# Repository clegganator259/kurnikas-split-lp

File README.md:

# kurnikas-split-lp
My attempt at designing my perfect split ergo keyboard

# Attribution

For the battery connector and led footprints @celolides fantastic [footprint library](https://github.com/ceoloide/ergogen-footprints)
For the choc v1 reversible footprints @ergogen + @infused-kim, @ceoloide, @grazfather, @nxtk improvements

For the videos that helped make this possible [Christian Sellig's wonderful video](https://www.youtube.com/watch?v=7UXsD7nSfDY)
# BOM
## PCB Components
|Component                            |                    Quantity|
|-------------------------------------|---------------------------:|
|kurnikas-split-lp PCB                |                           2|
|Nice nano v2 compatible board        |                           2|
|Choc v1 Key switches                 |                          64|
|SK6812 mini-e RGB                    |                          64|
|EC12/EC11 low profile encoder        |                           2|
|1N4148W SOD123 Diodes                | 64/66 if using EC11 Encoder|
|JST PH2 board connector              |                           2|
|3.7v Lipo battery thickness < 8mm    |                           2|
|JST PH2 male connectors for batteries|                           2|
|7 pin on/off toggle slide switch     |                           2|
|SKQGABE010 touch switch smd          |                           2|

## Case components
### Full case
|Component         | Quantity|
|------------------|--------:|
|8mm m2 standoffs  |       10|
|m2 flat top screws|       10|
|[Left hand faceplate](production/full-case-3dprint/face-plate-left.stl)| 1|
|[Right hand faceplate](production/full-case-3dprint/face-plate-right.stl)| 1|
|[Left hand Backplate](production/full-case-3dprint/base-plate-right.stl)| 1|
|[Right hand Backplate](production/full-case-3dprint/base-plate-left.stl)| 1|

### Sandwich Case
|Component                             | Quantity|
|--------------------------------------|--------:|
|m2x4mm chicago screws with max 3mm OD |       10|
|Faceplate ([laser cut](production/sandwich-case-laser-cut/faceplate.dxf)/[3d printed](production/sandwich-case-3dprint/faceplate.stl)) |2|
|Baseplate ([laser cut](production/sandwich-case-laser-cut/baseplate.dxf)/[3d printed](production/sandwich-case-3dprint/baseplate.stl)) |2|

## Making your own

For a more detailed tutorial please go to [the build tutorial](docs/tutorial.md)

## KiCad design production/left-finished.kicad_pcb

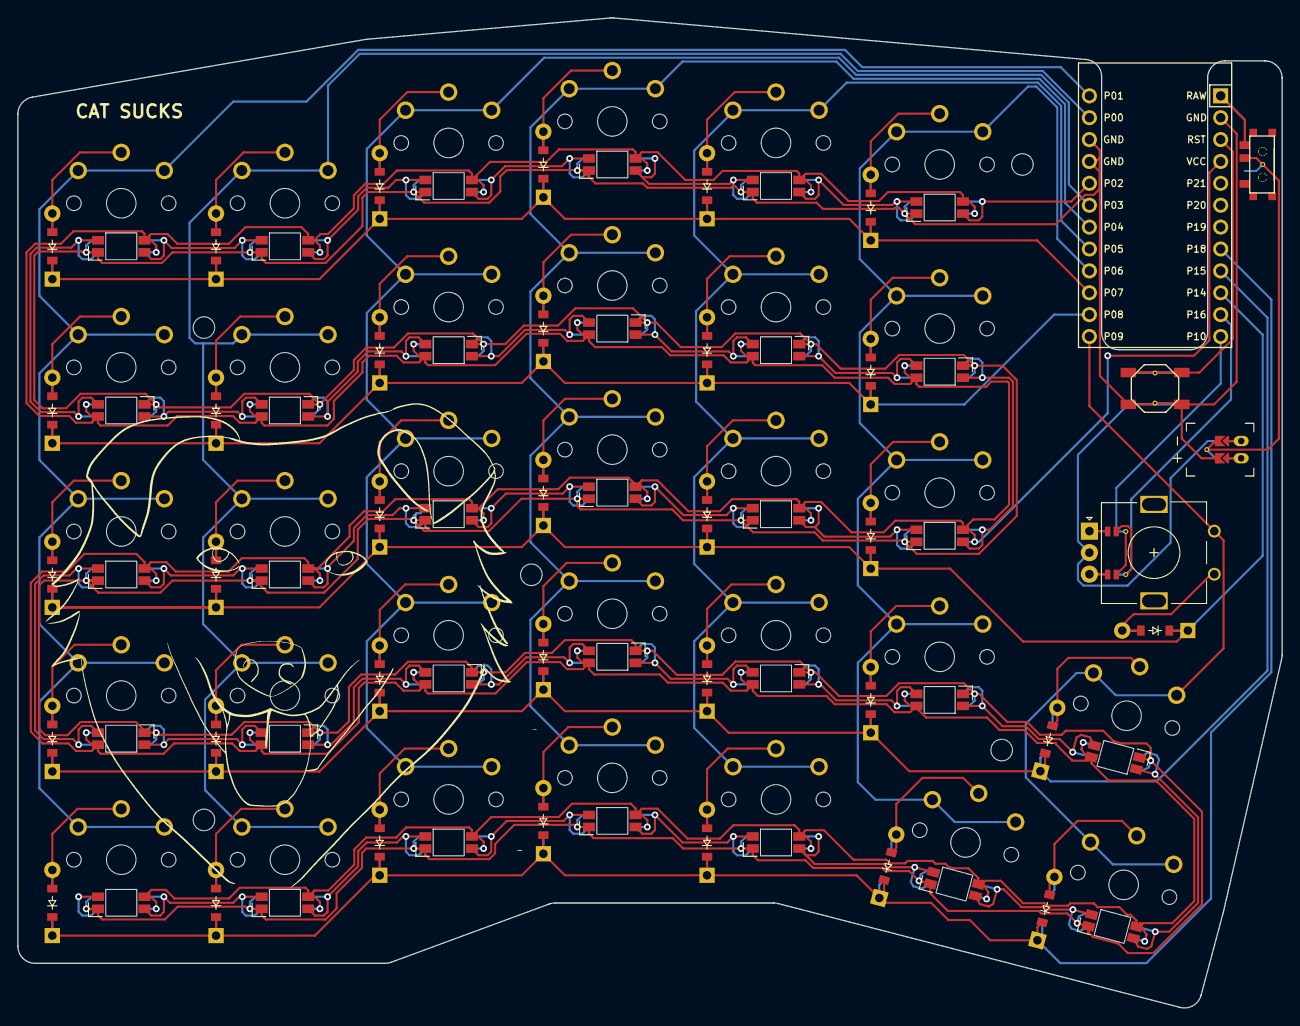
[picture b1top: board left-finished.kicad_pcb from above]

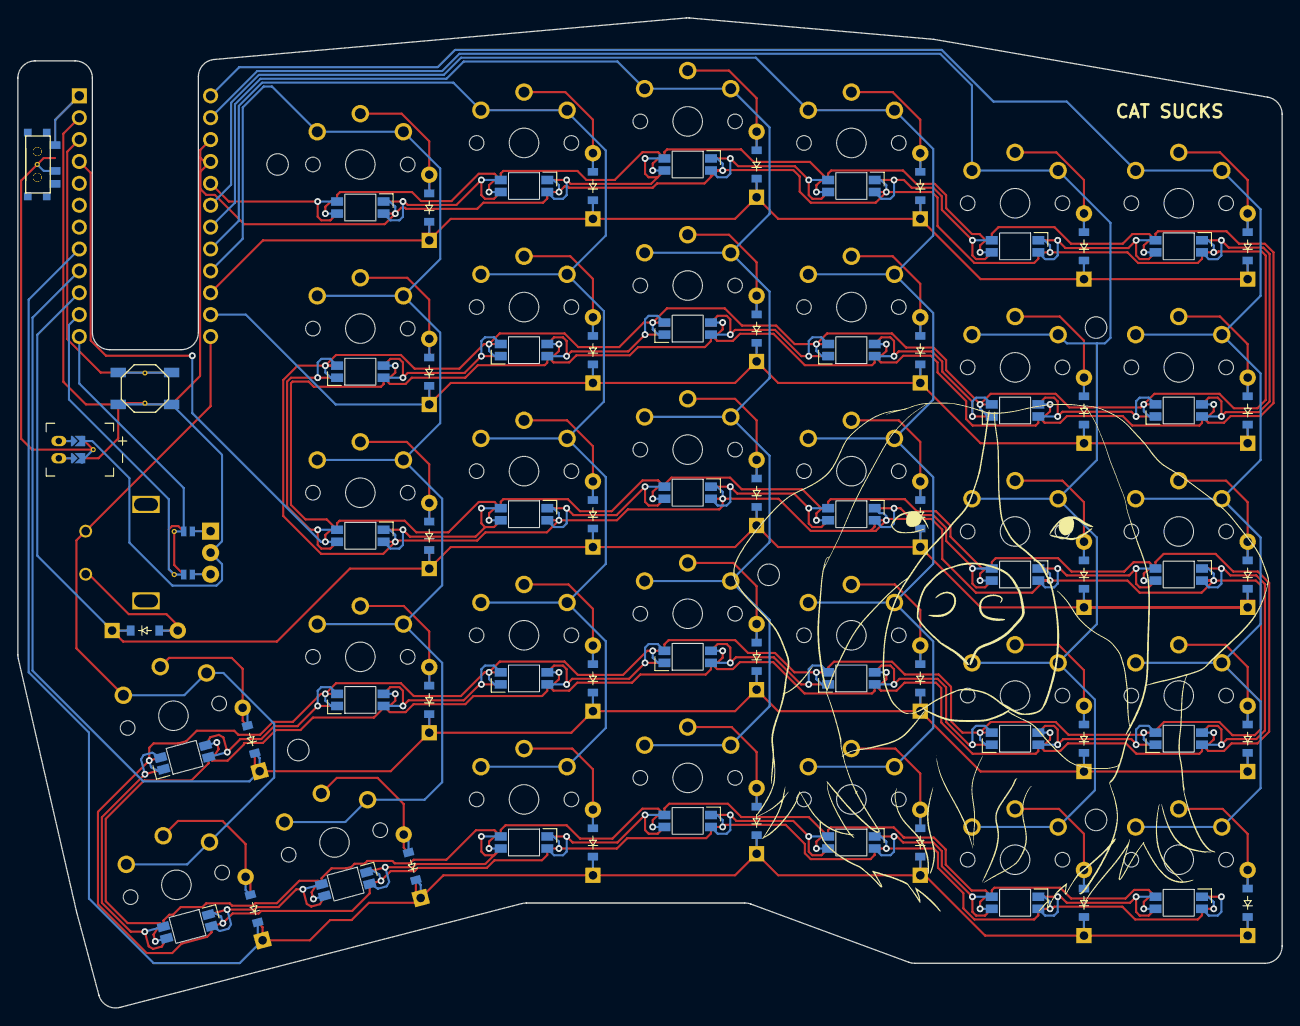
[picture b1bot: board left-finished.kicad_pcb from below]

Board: 2 copper layers, 146.8 x 114.9 mm, 108 parts (32 on the bottom side), 88 nets.

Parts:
B1, B2: SW_TACT_ALPS_SKQGABE010
D1, D2, D3, D4, D5, D6, D7, D8, D9, D10, D11, D12, D13, D14, D15, D16, D17, D18, D19, D20, D21, D22, D23, D24, D25, D26, D27, D28, D29, D30, D31, D32, D33: ComboDiode
J1, J2, J3, J4: Jumper
JST1: battery_connector_jst_ph_2
LED1, LED2, LED3, LED4, LED5, LED6, LED7, LED8, LED9, LED10, LED11, LED12, LED13, LED14, LED15, LED16, LED17, LED18, LED19, LED20, LED21, LED22, LED23, LED24, LED25, LED26, LED27, LED28, LED29, LED30, LED31, LED32: led_SK6812mini-e (per-key, reversible)
MCU1: ProMicro
ROT1: rotary_encoder
S1, S2, S3, S4, S5, S6, S7, S8, S9, S10, S11, S12, S13, S14, S15, S16, S17, S18, S19, S20, S21, S22, S23, S24, S25, S26, S27, S28, S29, S30, S31, S32: PG1350
T1, T2: SPDT_C128955

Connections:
GND: B1.1, B2.1, JST1.2, LED1.3, LED2.3, LED3.3, LED4.3, LED5.3, LED6.3, LED7.3, LED8.3, LED9.3, LED10.3, LED11.3, LED12.3, LED13.3, LED14.3, LED15.3, LED16.3, LED17.3, LED18.3, LED19.3, LED20.3, LED21.3, LED22.3, LED23.3, LED24.3, LED25.3, LED26.3, LED27.3, LED28.3, LED29.3, LED30.3, LED31.3, LED32.3, MCU1.2, MCU1.15, MCU1.16, ROT1.C
JST1_1: JST1.11, JST1.21, JST1.31
JST1_2: JST1.12, JST1.22, JST1.32
P0: MCU1.14, S6.1, S7.1, S8.1, S9.1, S10.1
P1: MCU1.13, S1.1, S2.1, S3.1, S4.1, S5.1
P2: LED17.2, MCU1.17
P3: MCU1.18, S11.1, S12.1, S13.1, S14.1, S15.1
P4: MCU1.19, S16.1, S17.1, S18.1, S19.1, S20.1
P5: MCU1.20, S21.1, S22.1, S23.1, S24.1, S25.1
P6: MCU1.21, S26.1, S27.1, S28.1, S29.1, S30.1
P7: D5.1, D10.1, D15.1, D20.1, D25.1, D29.1, MCU1.22
P8: D4.1, D9.1, D14.1, D19.1, D24.1, D28.1, MCU1.23
P9: MCU1.24, ROT1.1, S31.1, S32.1
P10: J2.1, J3.1, MCU1.12
P14: D3.1, D8.1, D13.1, D18.1, D23.1, D27.1, D33.1, MCU1.10
P15: D2.1, D7.1, D12.1, D17.1, D22.1, D26.1, D32.1, MCU1.9
P16: J1.1, J4.1, MCU1.11
P18: D1.1, D6.1, D11.1, D16.1, D21.1, D30.1, D31.1, MCU1.8
RAW: MCU1.1, T1.3, T2.1
RB_ROW: D33.2, ROT1.2
RST: B1.2, B2.2, MCU1.3
VCC: LED1.1, LED2.1, LED3.1, LED4.1, LED5.1, LED6.1, LED7.1, LED8.1, LED9.1, LED10.1, LED11.1, LED12.1, LED13.1, LED14.1, LED15.1, LED16.1, LED17.1, LED18.1, LED19.1, LED20.1, LED21.1, LED22.1, LED23.1, LED24.1, LED25.1, LED26.1, LED27.1, LED28.1, LED29.1, LED30.1, LED31.1, LED32.1, MCU1.4
index_bottom: D22.2, S22.2
index_home: D23.2, S23.2
index_mod: D21.2, S21.2
index_num: D25.2, S25.2
index_top: D24.2, S24.2
inner_bottom: D26.2, S26.2
inner_bottom_thumbs: D31.2, S31.2
inner_home: D27.2, S27.2
inner_num: D29.2, S29.2
inner_top: D28.2, S28.2
inner_top_thumbs: D32.2, S32.2
led_1: LED15.2, LED17.4
led_2: LED12.2, LED15.4
led_3: LED9.2, LED12.4
led_4: LED6.2, LED9.4
led_5: LED3.2, LED6.4
led_6: LED3.4, LED21.2
led_7: LED21.4, LED23.2
led_8: LED23.4, LED25.2
led_9: LED25.4, LED27.2
led_10: LED27.4, LED29.2
led_11: LED29.4, LED31.2
led_12: LED16.2, LED31.4
led_13: LED14.2, LED16.4
led_14: LED11.2, LED14.4
led_15: LED8.2, LED11.4
led_16: LED5.2, LED8.4
led_17: LED2.2, LED5.4
led_18: LED2.4, LED20.2
led_19: LED20.4, LED22.2
led_20: LED22.4, LED24.2
led_21: LED24.4, LED26.2
led_22: LED26.4, LED28.2
led_23: LED28.4, LED30.2
led_24: LED30.4, LED32.2
led_25: LED19.2, LED32.4
led_26: LED18.2, LED19.4
led_27: LED13.2, LED18.4
led_28: LED10.2, LED13.4
led_29: LED7.2, LED10.4
led_30: LED4.2, LED7.4
led_31: LED1.2, LED4.4
middle_bottom: D17.2, S17.2
middle_home: D18.2, S18.2
middle_mod: D16.2, S16.2
middle_num: D20.2, S20.2
middle_top: D19.2, S19.2
outer_bottom: D2.2, S2.2
outer_bottom_thumbs: D30.2, S30.2
outer_home: D3.2, S3.2
outer_mod: D1.2, S1.2
outer_num: D5.2, S5.2
outer_top: D4.2, S4.2
pinky_bottom: D7.2, S7.2
pinky_home: D8.2, S8.2
pinky_mod: D6.2, S6.2
pinky_num: D10.2, S10.2
pinky_top: D9.2, S9.2
pos: JST1.1, T1.2, T2.2
ring_bottom: D12.2, S12.2
ring_home: D13.2, S13.2
ring_mod: D11.2, S11.2
ring_num: D15.2, S15.2
ring_top: D14.2, S14.2
scroll-j1: J1.2, J3.2, ROT1.A
scroll-j2: J2.2, J4.2, ROT1.B

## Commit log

2025-02-18 Files sent to fab v1
2025-03-19 Feat: Adding production files
2025-03-19 Feat: Some minor additions for creating cases
2025-03-19 Docs: Add bom
2025-03-24 Production ready
2025-03-26 Chore: Rename files for more consistent naming
2025-03-26 Docs: Starting README
2025-03-26 Fix: Fixing docs links
2025-04-01 Writing more docs
2025-04-01 Chore: Removing useless file
